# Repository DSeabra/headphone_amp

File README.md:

# headphone_amp
Guitar Headphone Amp

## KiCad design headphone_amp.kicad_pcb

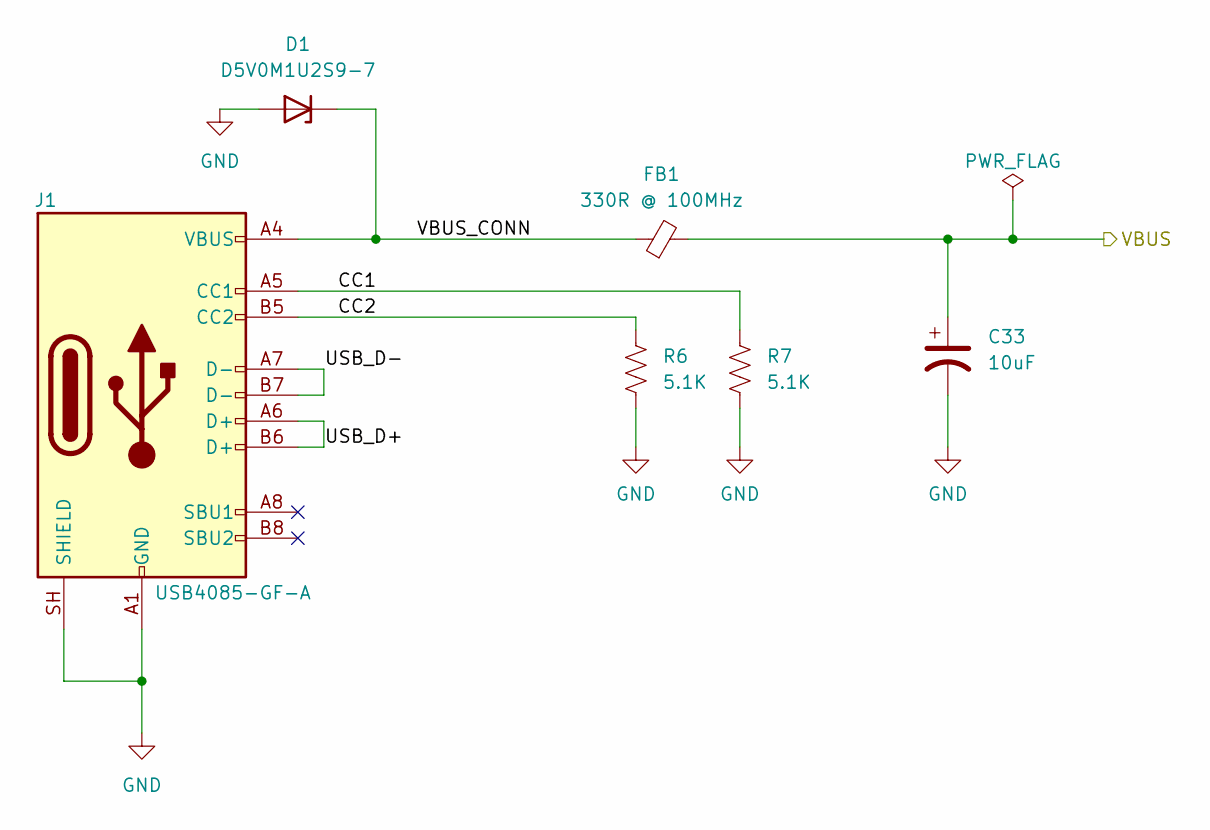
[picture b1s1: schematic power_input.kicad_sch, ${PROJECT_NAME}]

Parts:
C33: 10uF; TCJA_AVX
D1: D5V0M1U2S9-7; D_SOD-923
FB1: 330R @ 100MHz; L_0402_1005Metric
J1: USB4085-GF-A; USB_C_Receptacle_GCT_USB4085
R6, R7: 5.1K; R_0402_1005Metric

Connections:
/Power Input/CC1: J1.A5 (CC1), R7.1
/Power Input/CC2: J1.B5 (CC2), R6.1
/Power Input/USB_D+: J1.A6 (D+), J1.B6 (D+)
/Power Input/USB_D-: J1.A7 (D-), J1.B7 (D-)
/Power Input/VBUS_CONN: D1.1 (K), FB1.1, J1.A4 (VBUS), J1.A9 (VBUS), J1.B4 (VBUS), J1.B9 (VBUS)
/V_{BUS}: C33.1, FB1.2; also elsewhere on the board
GND: C33.2, D1.2 (A), J1.A1 (GND), J1.A12 (GND), J1.B1 (GND), J1.B12 (GND), J1.SH (SHIELD), R6.2, R7.2; also elsewhere on the board

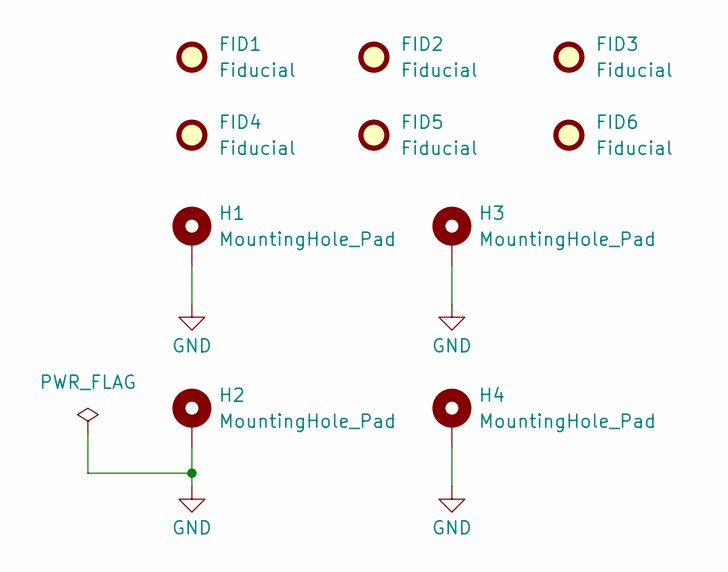
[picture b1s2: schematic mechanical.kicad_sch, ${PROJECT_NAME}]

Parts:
FID1, FID2, FID3, FID4, FID5, FID6: Fiducial; Fiducial_1.5mm_Mask3mm
H1, H2, H3, H4: MountingHole_Pad; MountingHole_3.2mm_M3_DIN965_Pad

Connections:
GND: H1.1 (1_1), H2.1 (1_1), H3.1 (1_1), H4.1 (1_1); also elsewhere on the board

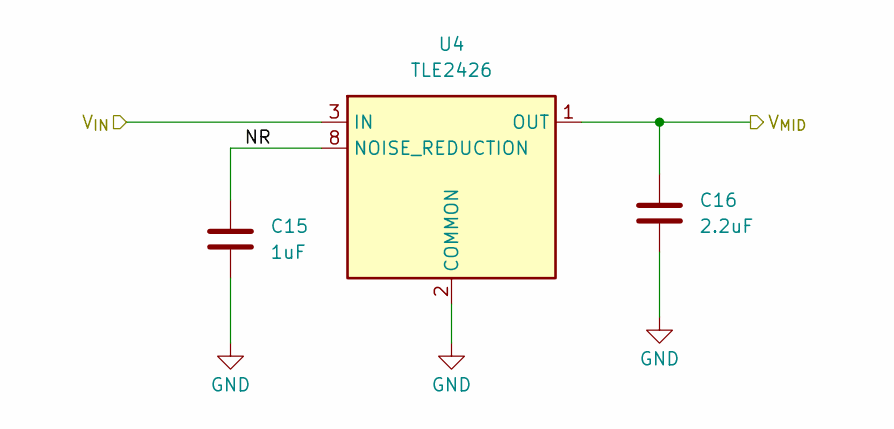
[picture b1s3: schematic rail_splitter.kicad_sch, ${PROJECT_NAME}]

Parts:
C15: 1uF; C_0603_1608Metric
C16: 2.2uF; C_0603_1608Metric
U4: TLE2426; SOIC-8_3.9x4.9mm_P1.27mm

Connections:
/Rail Splitter/NR: C15.2, U4.8 (NOISE_REDUCTION)
/V+: U4.3 (IN); also elsewhere on the board
/V_{MID}: C16.2, U4.1 (OUT); also elsewhere on the board
GND: C15.1, C16.1, U4.2 (COMMON); also elsewhere on the board

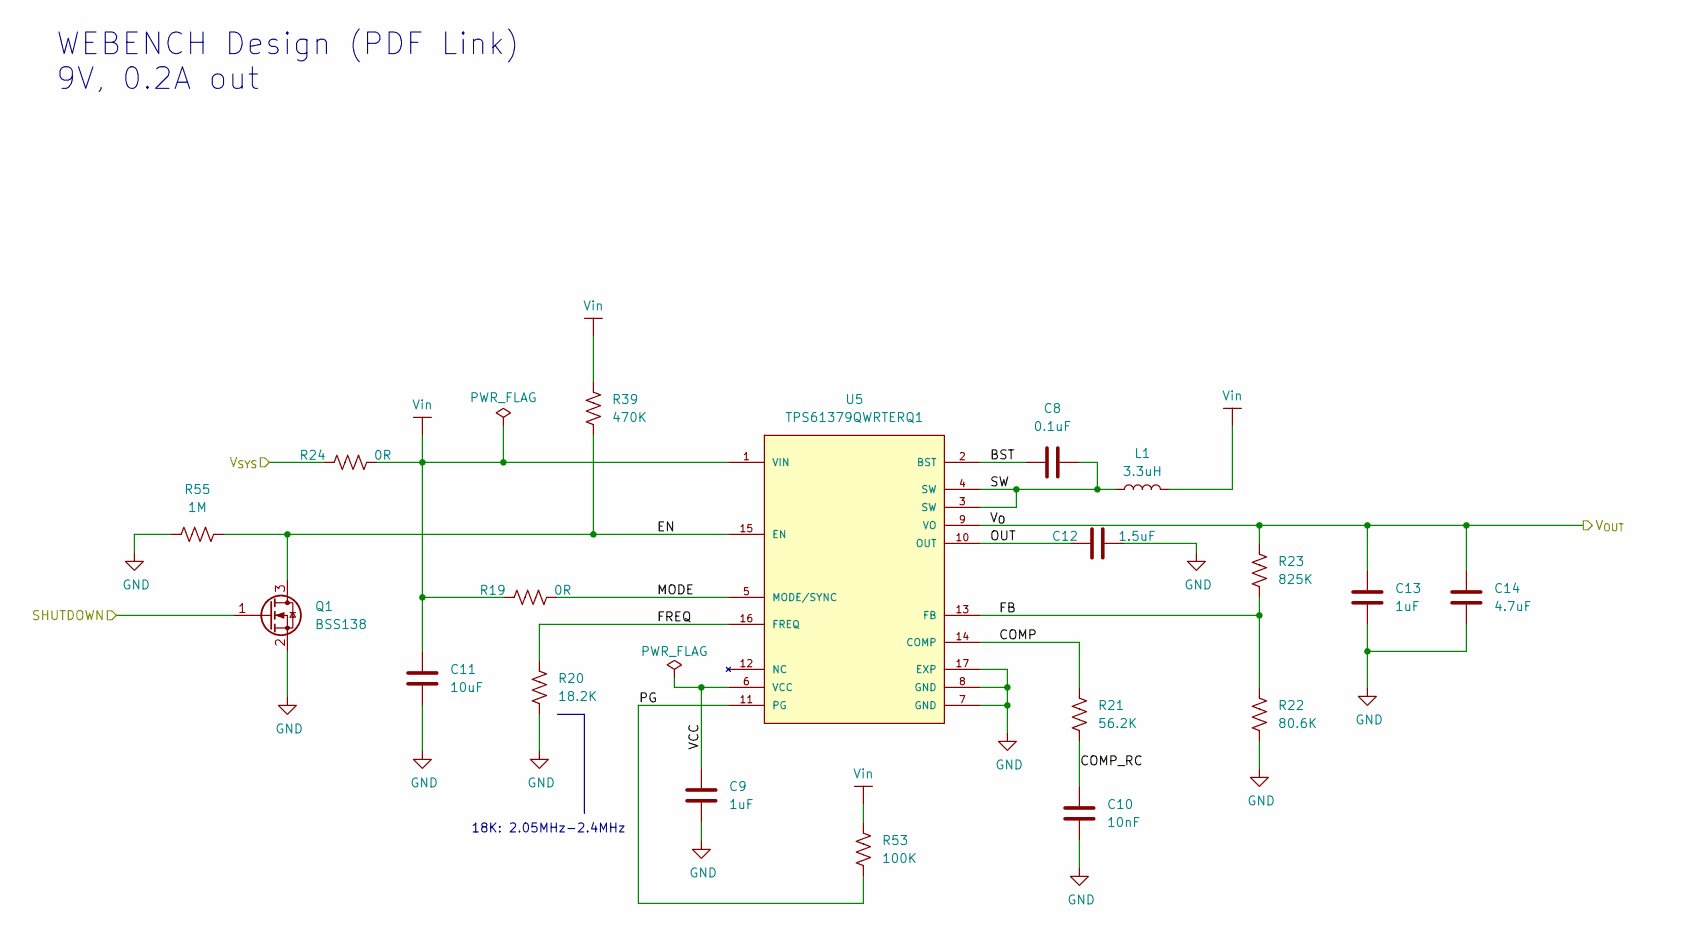
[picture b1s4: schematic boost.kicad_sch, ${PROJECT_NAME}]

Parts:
C8: 0.1uF; C_0402_1005Metric
C9, C13: 1uF; C_0402_1005Metric
C10: 10nF; C_0402_1005Metric
C11: 10uF; C_0805_2012Metric
C12: 1.5uF; C_0805_2012Metric
C14: 4.7uF; C_0603_1608Metric
L1: 3.3uH; L_1008_2520Metric
Q1: BSS138; SOT-23
R19, R24: 0R; R_0402_1005Metric
R20: 18.2K; R_0402_1005Metric
R21: 56.2K; R_0402_1005Metric
R22: 80.6K; R_0402_1005Metric
R23: 825K; R_0402_1005Metric
R39: 470K; R_0402_1005Metric
R53: 100K; R_0402_1005Metric
R55: 1M; R_0402_1005Metric
U5: TPS61379QWRTERQ1; VREG_TPS61379QWRTERQ1

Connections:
/Boost/BST: C8.1, U5.2 (BST)
/Boost/COMP: R21.2, U5.14 (COMP)
/Boost/COMP_RC: C10.1, R21.1
/Boost/EN: Q1.3 (D), R39.2, R55.2, U5.15 (EN)
/Boost/FB: R22.2, R23.1, U5.13 (FB)
/Boost/FREQ: R20.2, U5.16 (FREQ)
/Boost/MODE: R19.2, U5.5 (MODE/SYNC)
/Boost/OUT: C12.1, U5.10 (OUT)
/Boost/PG: R53.1, U5.11 (PG)
/Boost/SHUTDOWN: Q1.1 (G); also elsewhere on the board
/Boost/SW: C8.2, L1.1, U5.3 (SW), U5.4 (SW)
/Boost/VCC: C9.1, U5.6 (VCC)
/Boost/Vin: C11.2, L1.2, R19.1, R24.2, R39.1, R53.2, U5.1 (VIN)
/V+: C13.2, C14.2, R23.2, U5.9 (VO); also elsewhere on the board
/V_{SYS}: R24.1; also elsewhere on the board
GND: C9.2, C10.2, C11.1, C12.2, C13.1, C14.1, Q1.2 (S), R20.1, R22.1, R55.1, U5.7 (GND), U5.8 (GND), U5.17 (EXP); also elsewhere on the board

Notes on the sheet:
WEBENCH Design (PDF Link) 9V, 0.2A out
18K: 2.05MHz-2.4MHz

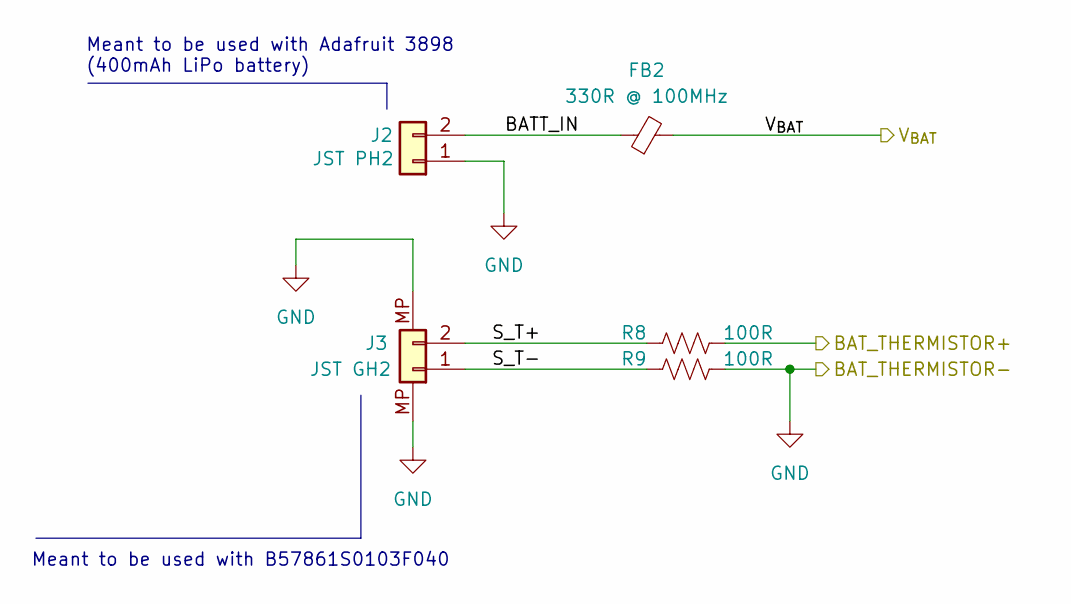
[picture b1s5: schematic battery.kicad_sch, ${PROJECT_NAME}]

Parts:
FB2: 330R @ 100MHz; L_0402_1005Metric
J2: JST PH2; JST_PH_S2B-PH-K_1x02_P2.00mm_Horizontal
J3: JST GH2; JST_GH_SM02B-GHS-TB_1x02-1MP_P1.25mm_Horizontal
R8, R9: 100R; R_0402_1005Metric

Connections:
/Battery Charger/TS+: R8.2; also elsewhere on the board
/Battery/BATT_IN: FB2.1, J2.2
/Battery/S_T+: J3.2, R8.1
/Battery/S_T-: J3.1, R9.1
/V_{BAT}: FB2.2; also elsewhere on the board
GND: J2.1, J3.MP, R9.2; also elsewhere on the board

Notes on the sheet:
Meant to be used with B57861S0103F040
Meant to be used with Adafruit 3898 (400mAh LiPo battery)

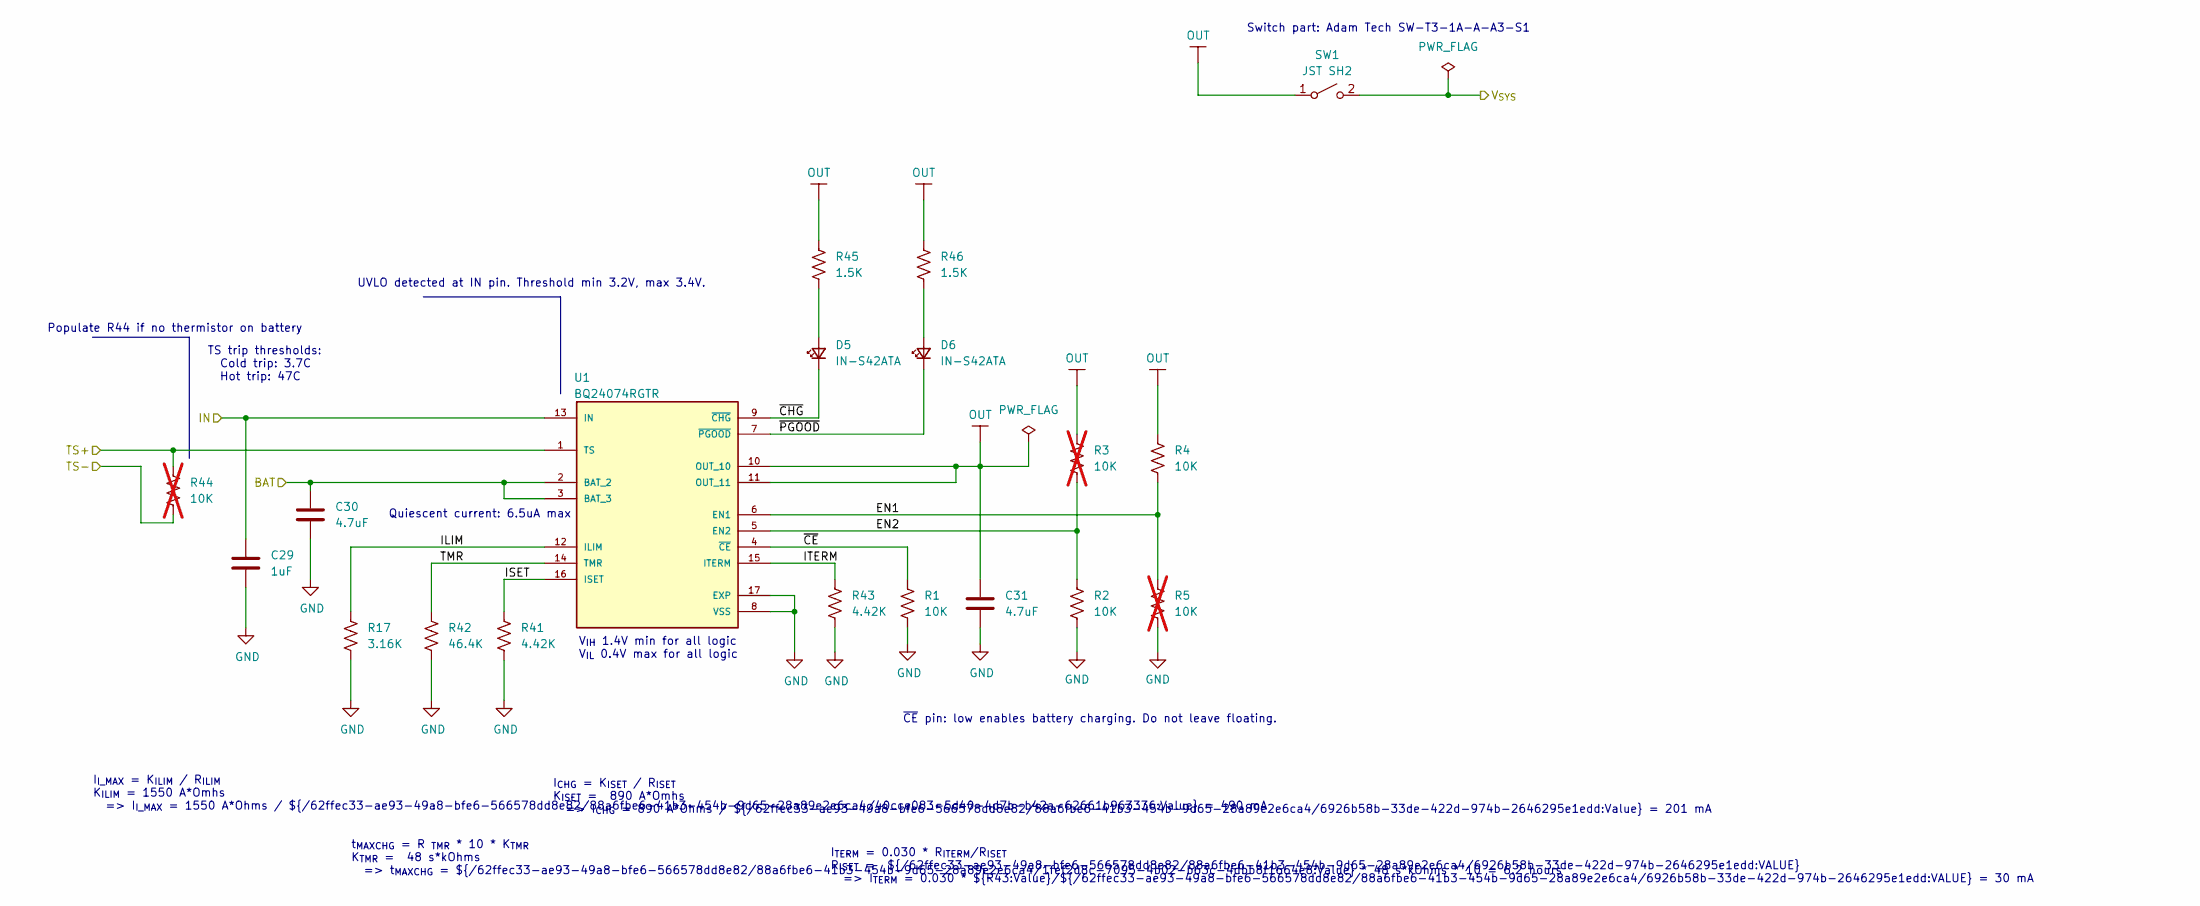
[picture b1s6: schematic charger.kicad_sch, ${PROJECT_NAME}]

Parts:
C29: 1uF; C_0402_1005Metric
C30, C31: 4.7uF; C_0603_1608Metric
D5, D6: IN-S42ATA; LED_0402_1005Metric
R1, R2, R4: 10K; R_0402_1005Metric
R3, R5, R44: 10K; R_0402_1005Metric; not fitted
R17: 3.16K; R_0402_1005Metric
R41, R43: 4.42K; R_0402_1005Metric
R42: 46.4K; R_0402_1005Metric
R45, R46: 1.5K; R_0402_1005Metric
SW1: JST SH2; JST_SH_BM02B-SRSS-TB_1x02-1MP_P1.00mm_Vertical
U1: BQ24074RGTR; bq24074rgtr

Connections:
/Battery Charger/EN1: R4.2, R5.1, U1.6 (EN1)
/Battery Charger/EN2: R2.1, R3.2, U1.5 (EN2)
/Battery Charger/ILIM: R17.1, U1.12 (ILIM)
/Battery Charger/ISET: R41.2, U1.16 (ISET)
/Battery Charger/ITERM: R43.2, U1.15 (ITERM)
/Battery Charger/OUT: C31.2, R3.1, R4.1, R45.2, R46.2, SW1.1 (A), U1.10 (OUT_10), U1.11 (OUT_11)
/Battery Charger/TMR: R42.2, U1.14 (TMR)
/Battery Charger/TS+: R44.1, U1.1 (TS); also elsewhere on the board
/Battery Charger/~CE: R1.1, U1.4 (~CE)
/Battery Charger/~CHG: D5.1 (K), U1.9 (~CHG)
/Battery Charger/~PGOOD: D6.1 (K), U1.7 (~PGOOD)
/V_{BAT}: C30.2, U1.2 (BAT_2), U1.3 (BAT_3); also elsewhere on the board
/V_{BUS}: C29.2, U1.13 (IN); also elsewhere on the board
/V_{SYS}: SW1.2 (B); also elsewhere on the board
GND: C29.1, C30.1, C31.1, R1.2, R2.2, R5.2, R17.2, R41.1, R42.1, R43.1, R44.2, U1.8 (VSS), U1.17 (EXP); also elsewhere on the board
unnamed: D5.2 (A), R45.1
unnamed: D6.2 (A), R46.1

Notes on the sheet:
~{CE} pin: low enables battery charging. Do not leave floating.
Quiescent current: 6.5uA max
V_{IH} 1.4V min for all logic V_{IL} 0.4V max for all logic
UVLO detected at IN pin. Threshold min 3.2V, max 3.4V.
I_{TERM} = 0.030 * R_{ITERM}/R_{ISET} R_{ISET} = ${/62ffec33-ae93-49a8-bfe6-566578dd8e82/88a6fbe6-41b3-454b-9d65-28a89e2e6ca4/6926b58b-33de-422d-974b-2646295e1edd:VALUE} => I_{TERM} = 0.030 * ${R43:Value}/${/62ffec33-ae93-49a8-bfe6-566578dd8e82/88a6fbe6-41b3-454b-9d65-28a89e2e6ca4/6926b58b-33de-422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
TS trip thresholds: Cold trip: 3.7C Hot trip: 47C
t_{MAXCHG} = R _{TMR} * 10 * K_{TMR} K_{TMR} = 48 s*kOhms => t_{MAXCHG} = ${/62ffec33-ae93-49a8-bfe6-566578dd8e82/88a6fbe6-41b3-454b-9d65-28a89e2e6ca4/1fef2d8c-7095-4b02-b63c-4dbb8f1664e8:Value} * 48 s*kOhms * 10 = 6.2 hours
Switch part: Adam Tech SW-T3-1A-A-A3-S1
I_{I_MAX} = K_{ILIM} / R_{ILIM} K_{ILIM} = 1550 A*Omhs => I_{I_MAX} = 1550 A*Ohms / ${/62ffec33-ae93-49a8-bfe6-566578dd8e82/88a6fbe6-41b3-454b-9d65-28a89e2e6ca4/40cce083-5d40-4d7b-b42a-62661b963336:Value} = 490 mA
Populate R44 if no thermistor on battery
I_{CHG} = K_{ISET} / R_{ISET} K_{ISET} = 890 A*Omhs => I_{CHG} = 890 A*Ohms / ${/62ffec33-ae93-49a8-bfe6-566578dd8e82/88a6fbe6-41b3-454b-9d65-28a89e2e6ca4/6926b58b-33de-422d-974b-2646295e1edd:Value} = 201 mA

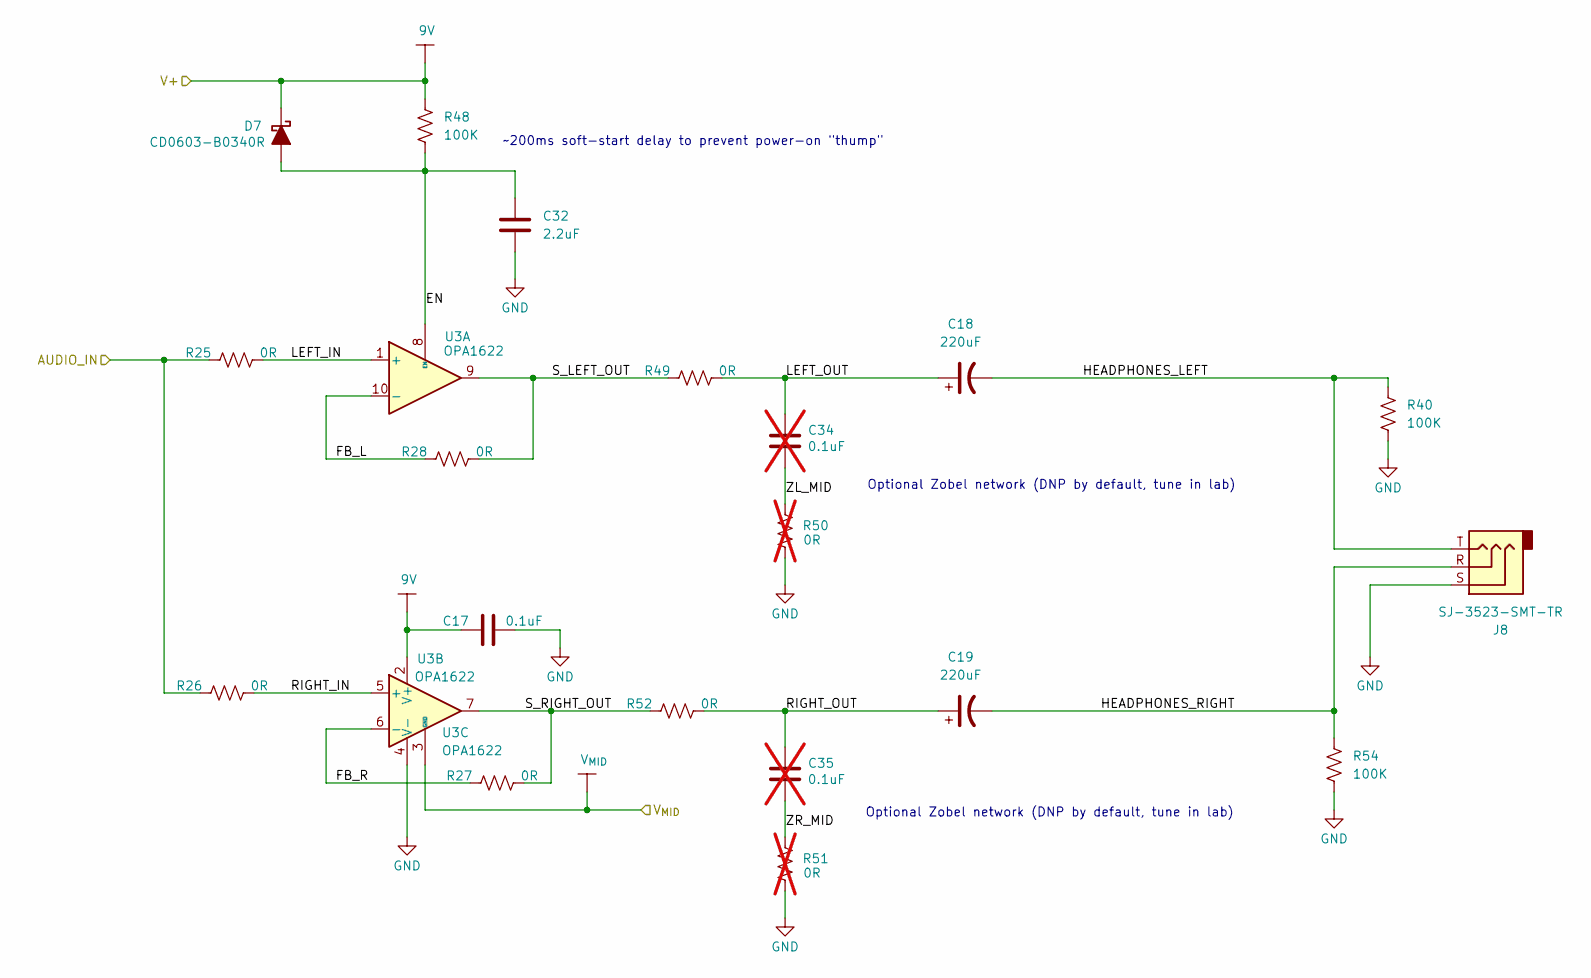
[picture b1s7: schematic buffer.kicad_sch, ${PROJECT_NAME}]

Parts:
C17: 0.1uF; C_0402_1005Metric
C18, C19: 220uF; WCAP-PSLP_6.3X5.8_DXL_
C32: 2.2uF; C_0603_1608Metric
C34, C35: 0.1uF; C_0402_1005Metric; not fitted
D7: CD0603-B0340R; D_0603_1608Metric
J8: SJ-3523-SMT-TR; Jack_3.5mm_CUI_SJ-3523-SMT_Horizontal
R25, R26, R27, R28, R49, R52: 0R; R_0402_1005Metric
R40, R48, R54: 100K; R_0402_1005Metric
R50, R51: 0R; R_0402_1005Metric; not fitted
U3: OPA1622; Texas_S-PVSON-N10

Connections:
/Audio Input/AUDIO_OUT: R25.1, R26.1; also elsewhere on the board
/Current Buffer/EN: C32.2, D7.2 (A), R48.1, U3.8 (EN)
/Current Buffer/FB_L: R28.1, U3.10 (-)
/Current Buffer/FB_R: R27.1, U3.6 (-)
/Current Buffer/HEADPHONES_LEFT: C18.2, J8.T, R40.1
/Current Buffer/HEADPHONES_RIGHT: C19.2, J8.R, R54.1
/Current Buffer/LEFT_IN: R25.2, U3.1 (+)
/Current Buffer/LEFT_OUT: C18.1, C34.2, R49.2
/Current Buffer/RIGHT_IN: R26.2, U3.5 (+)
/Current Buffer/RIGHT_OUT: C19.1, C35.2, R52.2
/Current Buffer/S_LEFT_OUT: R28.2, R49.1, U3.9
/Current Buffer/S_RIGHT_OUT: R27.2, R52.1, U3.7
/Current Buffer/ZL_MID: C34.1, R50.2
/Current Buffer/ZR_MID: C35.1, R51.2
/V+: C17.1, D7.1 (K), R48.2, U3.2 (V+); also elsewhere on the board
/V_{MID}: U3.3 (GND); also elsewhere on the board
GND: C17.2, C32.1, J8.S, R40.2, R50.1, R51.1, R54.2, U3.4 (V-), U3.11 (V-); also elsewhere on the board

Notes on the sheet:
Optional Zobel network (DNP by default, tune in lab)
~200ms soft-start delay to prevent power-on "thump"

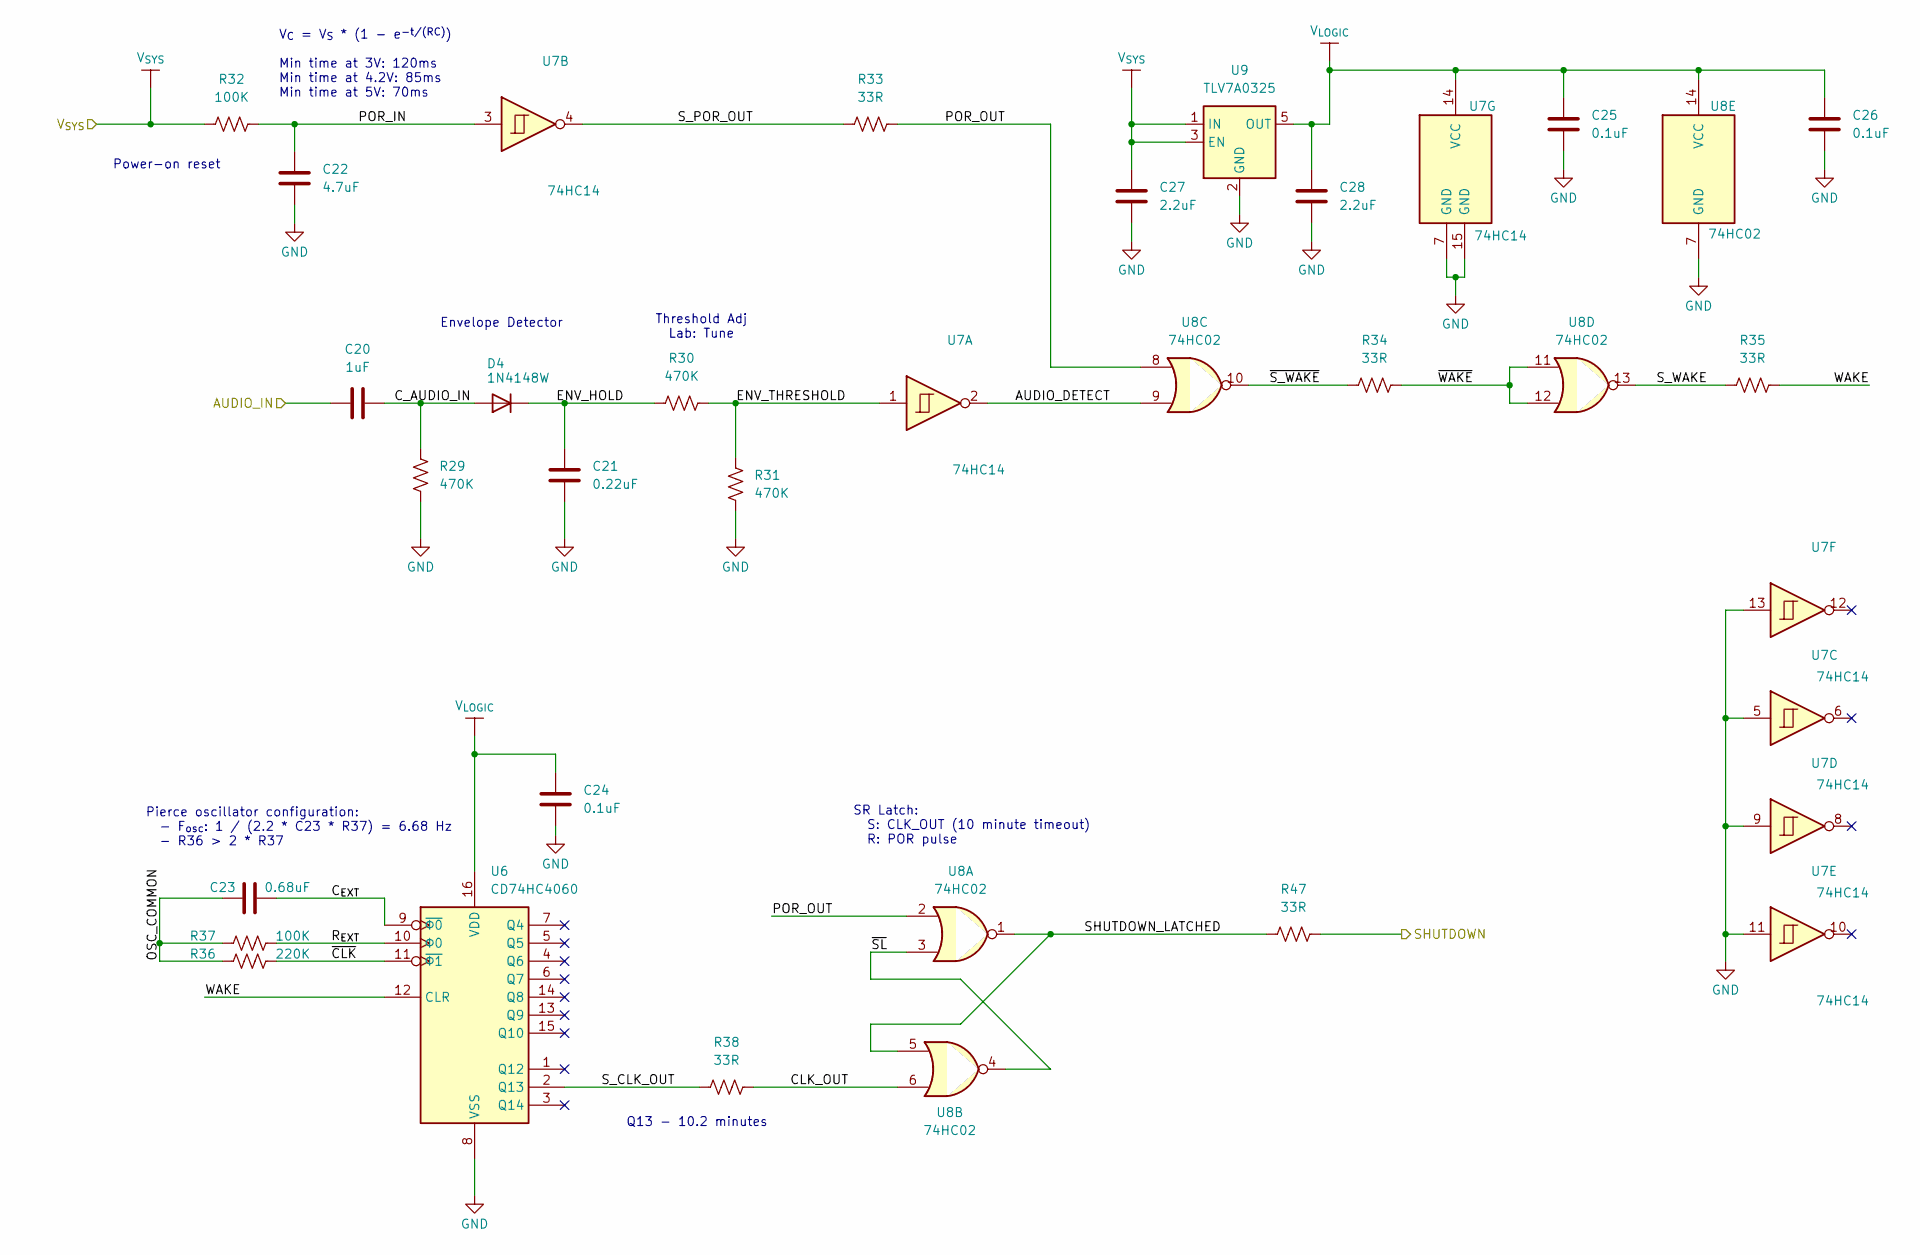
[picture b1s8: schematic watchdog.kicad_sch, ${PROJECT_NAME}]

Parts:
C20: 1uF; C_0603_1608Metric
C21: 0.22uF; C_0402_1005Metric
C22: 4.7uF; C_0603_1608Metric
C23: 0.68uF; C_0402_1005Metric
C24, C25, C26: 0.1uF; C_0402_1005Metric
C27, C28: 2.2uF; C_0603_1608Metric
D4: 1N4148W; D_SOD-123
R29, R30, R31: 470K; R_0402_1005Metric
R32, R37: 100K; R_0402_1005Metric
R33, R34, R35, R38, R47: 33R; R_0402_1005Metric
R36: 220K; R_0402_1005Metric
U6: CD74HC4060; TSSOP-16_4.4x5mm_P0.65mm
U7: 74HC14; DHVQFN14_SOT762-1_NEX
U8: 74HC02; TSSOP-14_4.4x5mm_P0.65mm
U9: TLV7A0325; SOT-23-5

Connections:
/Audio Input/SECOND_STAGE_OUT: C20.2; also elsewhere on the board
/Boost/SHUTDOWN: R47.1; also elsewhere on the board
/V_{SYS}: C27.2, R32.1, U9.1 (IN), U9.3 (EN); also elsewhere on the board
/Watchdog/AUDIO_DETECT: U7.2, U8.9
/Watchdog/CLK_OUT: R38.1, U8.6
/Watchdog/C_AUDIO_IN: C20.1, D4.2 (A), R29.2
/Watchdog/C_{EXT}: C23.1, U6.9 (~Φ0)
/Watchdog/ENV_HOLD: C21.1, D4.1 (K), R30.2
/Watchdog/ENV_THRESHOLD: R30.1, R31.1, U7.1
/Watchdog/OSC_COMMON: C23.2, R36.2, R37.2
/Watchdog/POR_IN: C22.2, R32.2, U7.3
/Watchdog/POR_OUT: R33.1, U8.2, U8.8
/Watchdog/R_{EXT}: R37.1, U6.10 (Φ0)
/Watchdog/SHUTDOWN_LATCHED: R47.2, U8.1, U8.5
/Watchdog/S_CLK_OUT: R38.2, U6.2 (Q13)
/Watchdog/S_POR_OUT: R33.2, U7.4
/Watchdog/S_WAKE: R35.2, U8.13
/Watchdog/V_{LOGIC}: C24.1, C25.1, C26.1, C28.2, U6.16 (VDD), U7.14 (VCC), U8.14 (VCC), U9.5 (OUT)
/Watchdog/WAKE: R35.1, U6.12 (CLR)
/Watchdog/~CLK: R36.1, U6.11 (~Φ1)
/Watchdog/~SL: U8.3, U8.4
/Watchdog/~S_WAKE: R34.2, U8.10
/Watchdog/~WAKE: R34.1, U8.11, U8.12
GND: C21.2, C22.1, C24.2, C25.2, C26.2, C27.1, C28.1, R29.1, R31.2, U6.8 (VSS), U7.5, U7.7 (GND), U7.9, U7.11, U7.13, U7.15 (GND), U8.7 (GND), U9.2 (GND); also elsewhere on the board

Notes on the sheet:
Envelope Detector
Threshold Adj Lab: Tune
Q13 - 10.2 minutes
Power-on reset
V_{C} = V_{S} * (1 - e^{-t/(RC)}) Min time at 3V: 120ms Min time at 4.2V: 85ms Min time at 5V: 70ms
Pierce oscillator configuration: - F_{osc}: 1 / (2.2 * C23 * R37) = 6.68 Hz - R36 > 2 * R37
SR Latch: S: CLK_OUT (10 minute timeout) R: POR pulse

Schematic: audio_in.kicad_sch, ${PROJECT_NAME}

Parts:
C1: 0.1uF; C_0402_1005Metric
C2, C6: 0.1uF; C_1210_3225Metric
C3, C7: 470pF; C_0402_1005Metric
C4: 51pF; C_0402_1005Metric
C5: 47nF; C_0402_1005Metric
C36: 3.9nF; C_0603_1608Metric
D2, D3: 1N4148W; D_SOD-123; not fitted
FB3: 60R @ 2MHz; L_Wuerth_PMFI-201610
J4, J6: JST SH3; JST_SH_BM03B-SRSS-TB_1x03-1MP_P1.00mm_Vertical
J5: Header_2x1; PinHeader_2x01_P2.54mm_Vertical; not fitted
J7: 415-47-208-41-004000; PinSocket_2x04_P2.54mm_Vertical
J10: MJ-3523-SMT-TR; CONN_MJ-3523_CUD
JP1, JP2: SolderJumper_2_Open; SolderJumper-2_P1.3mm_Open_TrianglePad1.0x1.5mm
R10: 1K; R_0402_1005Metric
R11: 51K; R_0402_1005Metric
R12: 4.7K; R_0402_1005Metric
R13: 1M; R_0402_1005Metric
R14: 100K; R_0402_1005Metric
R15, R16: 33K; R_0402_1005Metric
R18: 10K; R_0402_1005Metric
U2: OPA1678; DRG0008A

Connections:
/Audio Input/AUDIO_OUT: J6.2; also elsewhere on the board
/Audio Input/FB_AC_COUPLE: C5.1, R12.2
/Audio Input/FB_RES: J4.1, R11.2
/Audio Input/FIRST_STAGE_FB: C4.1, J7.1, J7.8, R11.1, R12.1, U2.2 (-)
/Audio Input/FIRST_STAGE_IN: C2.2, R13.2, U2.3 (+)
/Audio Input/FIRST_STAGE_OUT: C4.2, C6.1, J4.2, J4.3, J7.4, J7.5, JP1.2 (B), JP2.2 (B), U2.1
/Audio Input/JACK_IN: J5.2, J10.2 (T), R10.1
/Audio Input/JACK_LPF: C2.1, C3.1, R10.2
/Audio Input/SECOND_STAGE_AC: C6.2, R15.1
/Audio Input/SECOND_STAGE_FILTERED: C36.1, J6.3, R18.2
/Audio Input/SECOND_STAGE_IN: C7.1, R14.1, R15.2, U2.6 (-)
/Audio Input/SECOND_STAGE_OUT: C7.2, D2.2 (A), D3.1 (K), R14.2, R18.1, U2.7; also elsewhere on the board
/Audio Input/SECOND_STAGE_P: R16.2, U2.5 (+)
/Audio Input/V_{+}F: C1.1, FB3.2, U2.8 (V+)
/V+: FB3.1; also elsewhere on the board
/V_{MID}: C5.2, C36.2, D2.1 (K), D3.2 (A), J6.1, R13.1, R16.1; also elsewhere on the board
GND: C1.2, C3.2, J4.MP, J5.1, J6.MP, J10.1 (S), U2.4 (V-), U2.9 (EP); also elsewhere on the board
unnamed: J7.2, J7.3, JP1.1 (A)
unnamed: J7.6, J7.7, JP2.1 (A)

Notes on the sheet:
PN: CB027D0104JBA
Optional "hard clipping"
Gain pot PN: PDB181-GTR02-504A2
Volume pot PN: PDB181-GTR01-103A2
AC-Coupling Cap: Choose Film!
Clipping diodes go here! (across feedback)
U2, in conjuction with R18 and C36, creates a second-order LPF at ~4kHz for a "cab filter" effect (removes harsh high-frequency "fizz")
Av = -R14 / R15 => Av = -100K / 33K = -3.03x
1N4148W-7-F
TODO: Check tip/sleeve
Av = 1 + (R11 + R_pot) / R12 Av_min (R_pot = 0): => Av_min = 1 + 51K/4.7K = 11.9x (21.5 dB) Av_max (R_pot = 500K): => Av_max = 1 + (51K + 500K)/4.7K = 118.2x (41.5 dB)

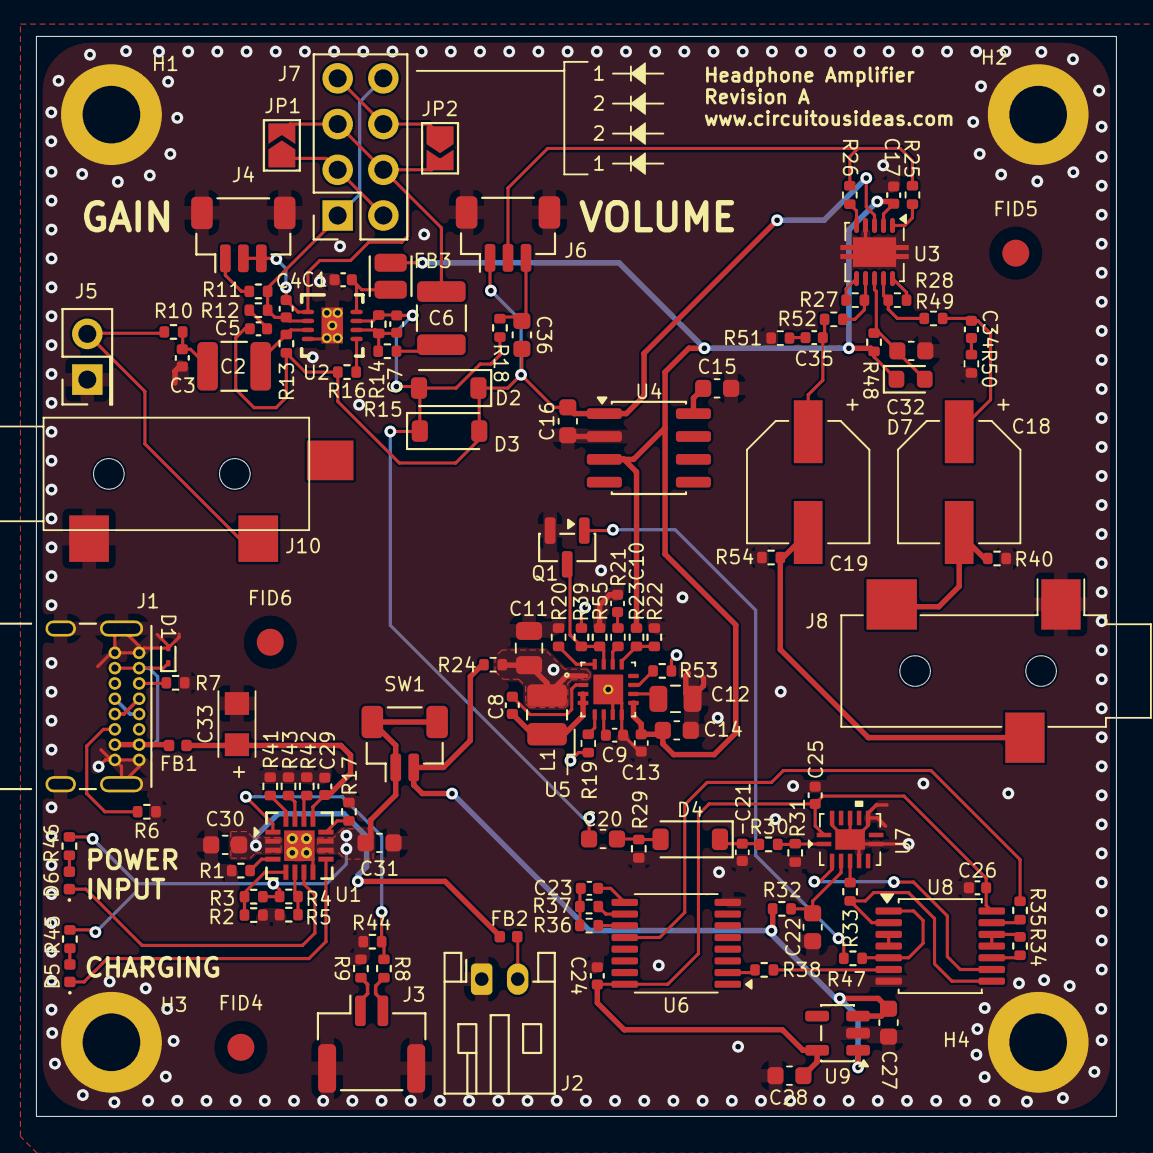
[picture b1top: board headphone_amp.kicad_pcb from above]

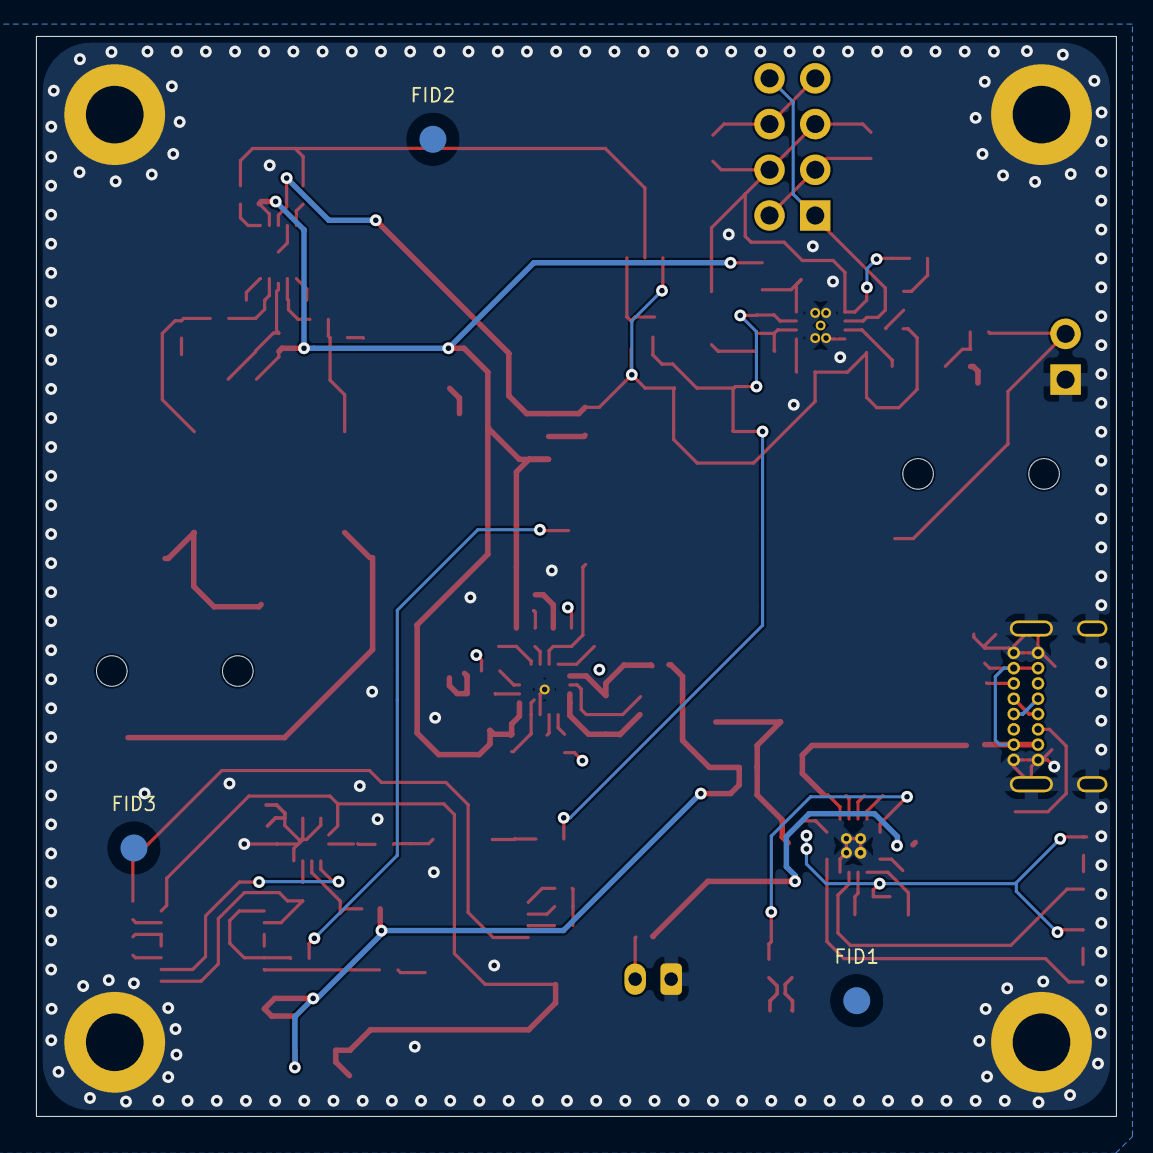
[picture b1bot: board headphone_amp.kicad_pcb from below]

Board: 4 copper layers, 60.0 x 60.0 mm, 134 parts (3 on the bottom side), 90 nets.
